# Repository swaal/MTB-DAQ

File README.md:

# MTB DAQ
A small and portable data acquisition system based on the PyBoard V1.1 designed to collect acceleration data while riding a mountain bike.

## About
The Mountain Bike Data Acquisition System (MTB DAQ) is a system designed to collect acceleration data while riding a mountain bike.
The system was designed as part of a Cal Poly Masters Thesis in Mechanical Engineering focused on a quantitative method for tuning mountain bike suspension. The MTB DAQ
was designed after the PyBoard V1.1 and is utilizes the same firmware. The acceleration data is stored in binary format on a Micro SD card. 

## Contents
The files included in this project provide almost everything needed to build a MTB DAQ. The folders are arranged as follows:
### BoardFiles
This folder contains all of the Autodesk Eagle schematic and board files. There are three types of boards: the Main Board, the UI Board, and the ADXL375 Board. 
The Main Board and UI Board work together to define the heart of the system, providing the computing power and user interface. The ADXL375 Board provides the necessary power filtering and connections for the ADXL375 accelerometer. The accelerometers are connected to the main board via two ethernet cables, chosen for their wide availability, low cost, and locking connection.
### MATLAB_Code
This folder contains two MATLAB files that can be used to interpret and plot the acceleration data from the binary files that are saved from the MTB DAQ.
### MicropythonCode
This folder contains the micropython files that run the MTB DAQ. Note that some of the files have been saved as *.mpy* files. This is a bytecote version of the original file. This was done in order to make the files small enough to fit in the flash memory of the microcontroller. The original files are contained within the sub folder "files_converted_to_mpy". Any modifications made to the original *.py* files can be converted into *.mpy* files using the python cross compiler *mpy-cross*. To get the system running, simply load on all the files in the MicropythonCode folder (excluding the contents in the files_converted_to_mpy subfolder) and reboot the board.
### PyBoardFirmware
A copy of the compatible PyBoard V1.1 firmware.

## Technical Specifications
- **Accelerometers:** Analog Devices ADXL375BCCZ Accelerometer
- **Number of Accelerometers Supported:** 2
- **Measurement Range:** +/- 200g
- **Output Data Rate:** 1600Hz (can be configured to go up to 3200Hz)
- **Battery Life:** > 8 hours

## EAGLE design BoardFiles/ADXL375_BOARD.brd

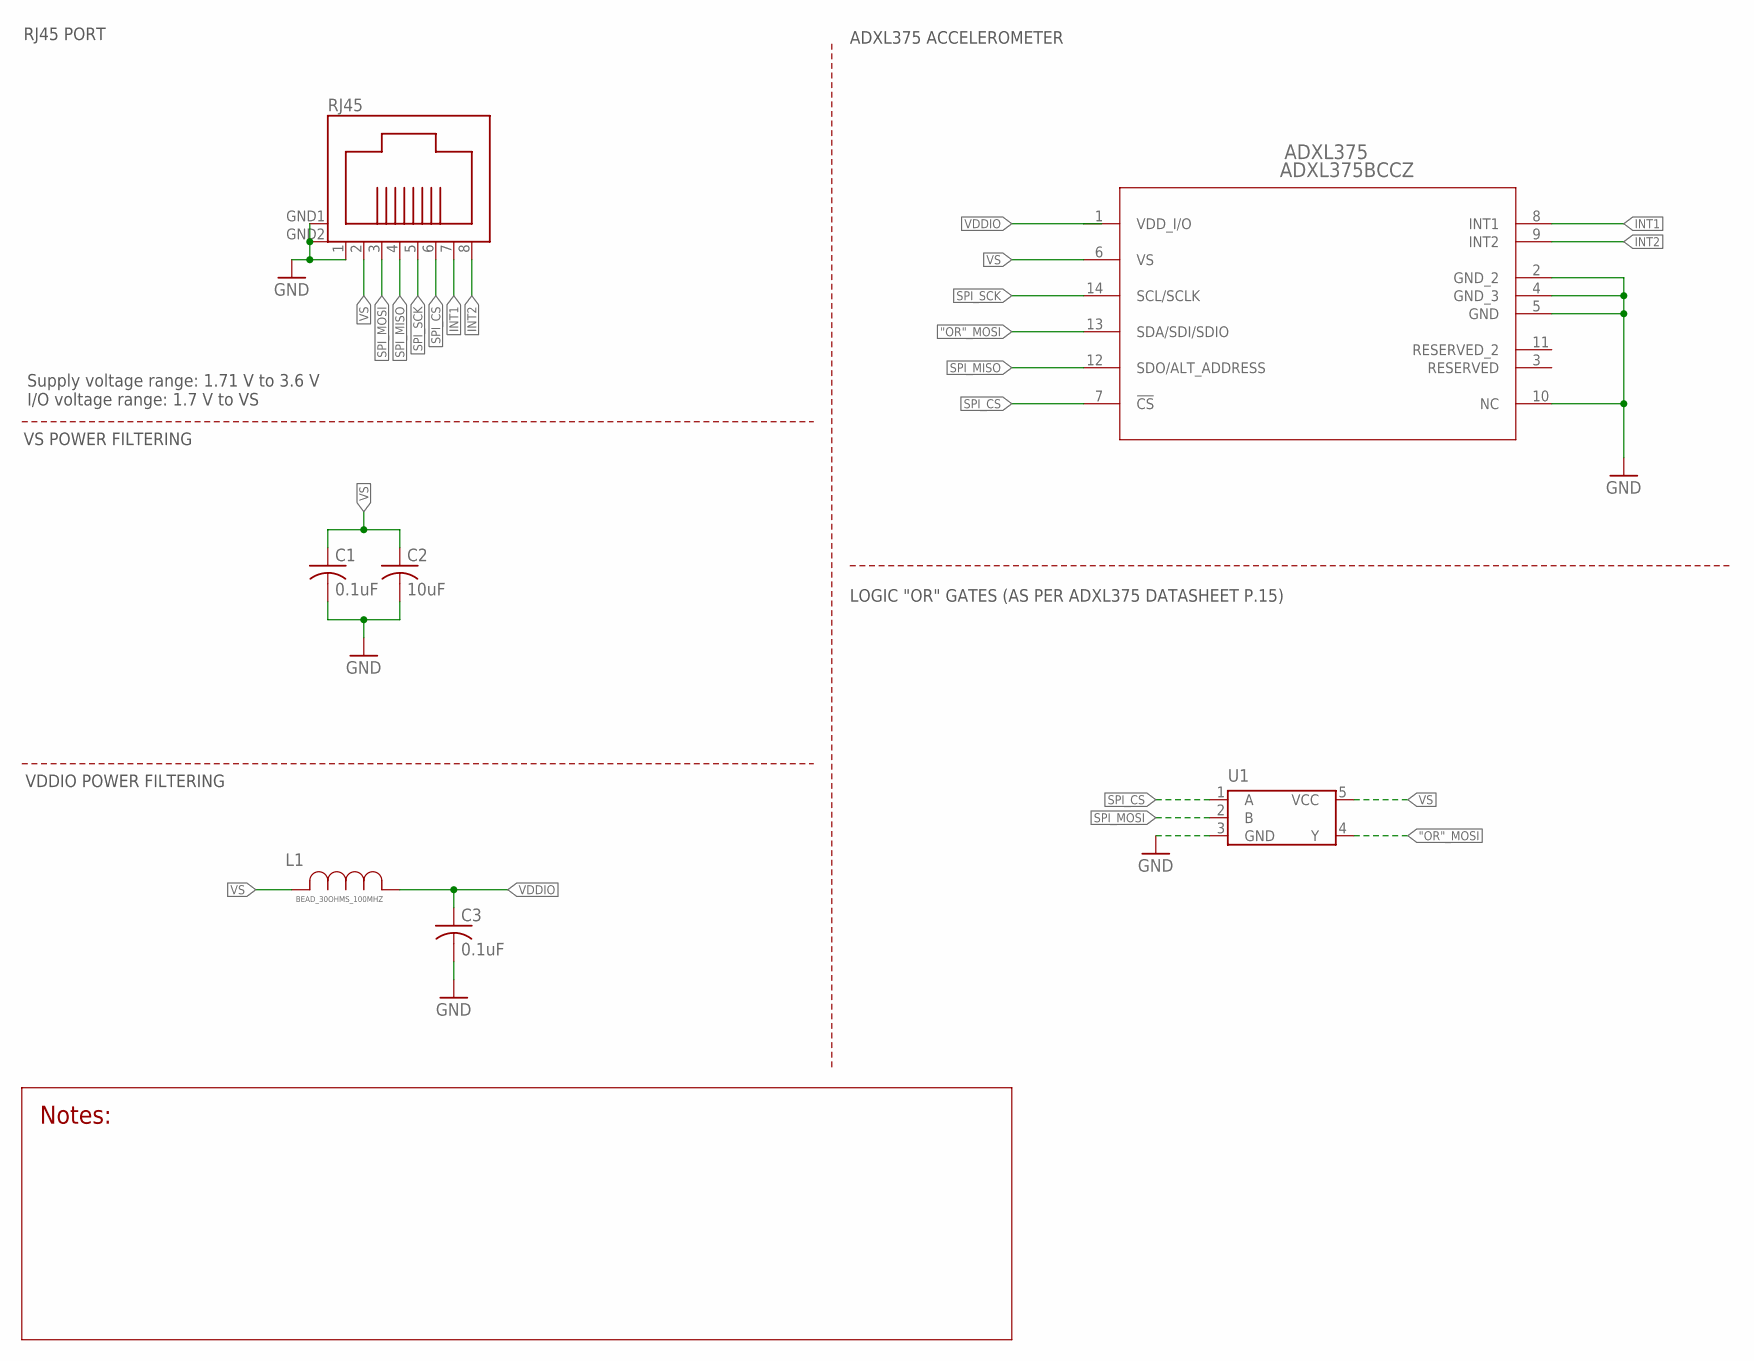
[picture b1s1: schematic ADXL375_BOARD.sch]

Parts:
ADXL375: ADXL375BCCZ; LGA_CC-14-1
C1, C3: 0.1uF; C0805
C2: 10uF; C0805
L1: BEAD_30OHMS_100MHZ; IND_BOURNS_MH2029
RJ45: RJ45_SURFACE_MOUNT
U1: SN74LVC1G32DCKR; DCK5

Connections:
"OR"_MOSI: ADXL375.13 (SDA/SDI/SDIO), U1.4 (Y)
GND: ADXL375.2 (GND_2), ADXL375.4 (GND_3), ADXL375.5 (GND), ADXL375.10 (NC), C1.2, C2.2, C3.2, RJ45.1, RJ45.GND1, RJ45.GND2, U1.3 (GND)
INT1: ADXL375.8 (INT1), RJ45.7
INT2: ADXL375.9 (INT2), RJ45.8
SPI_CS: ADXL375.7 (!CS), RJ45.6, U1.1 (A)
SPI_MISO: ADXL375.12 (SDO/ALT_ADDRESS), RJ45.4
SPI_MOSI: RJ45.3, U1.2 (B)
SPI_SCK: ADXL375.14 (SCL/SCLK), RJ45.5
VDDIO: ADXL375.1 (VDD_I/O), C3.1, L1.1
VS: ADXL375.6 (VS), C1.1, C2.1, L1.2, RJ45.2, U1.5 (VCC)

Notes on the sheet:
Supply voltage range: 1.71 V to 3.6 V I/O voltage range: 1.7 V to VS
RJ45 PORT
VS POWER FILTERING
VDDIO POWER FILTERING
LOGIC "OR" GATES (AS PER ADXL375 DATASHEET P.15)
ADXL375 ACCELEROMETER

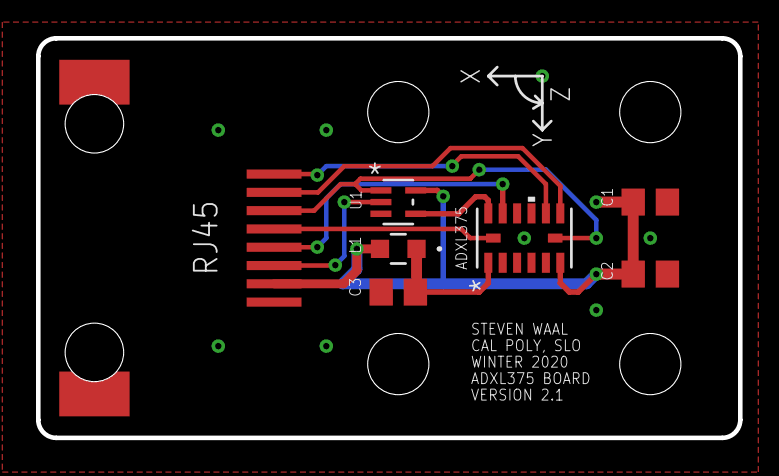
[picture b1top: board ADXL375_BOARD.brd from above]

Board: 2 copper layers, 39.0 x 22.2 mm, 7 parts (0 on the bottom side), 10 nets.

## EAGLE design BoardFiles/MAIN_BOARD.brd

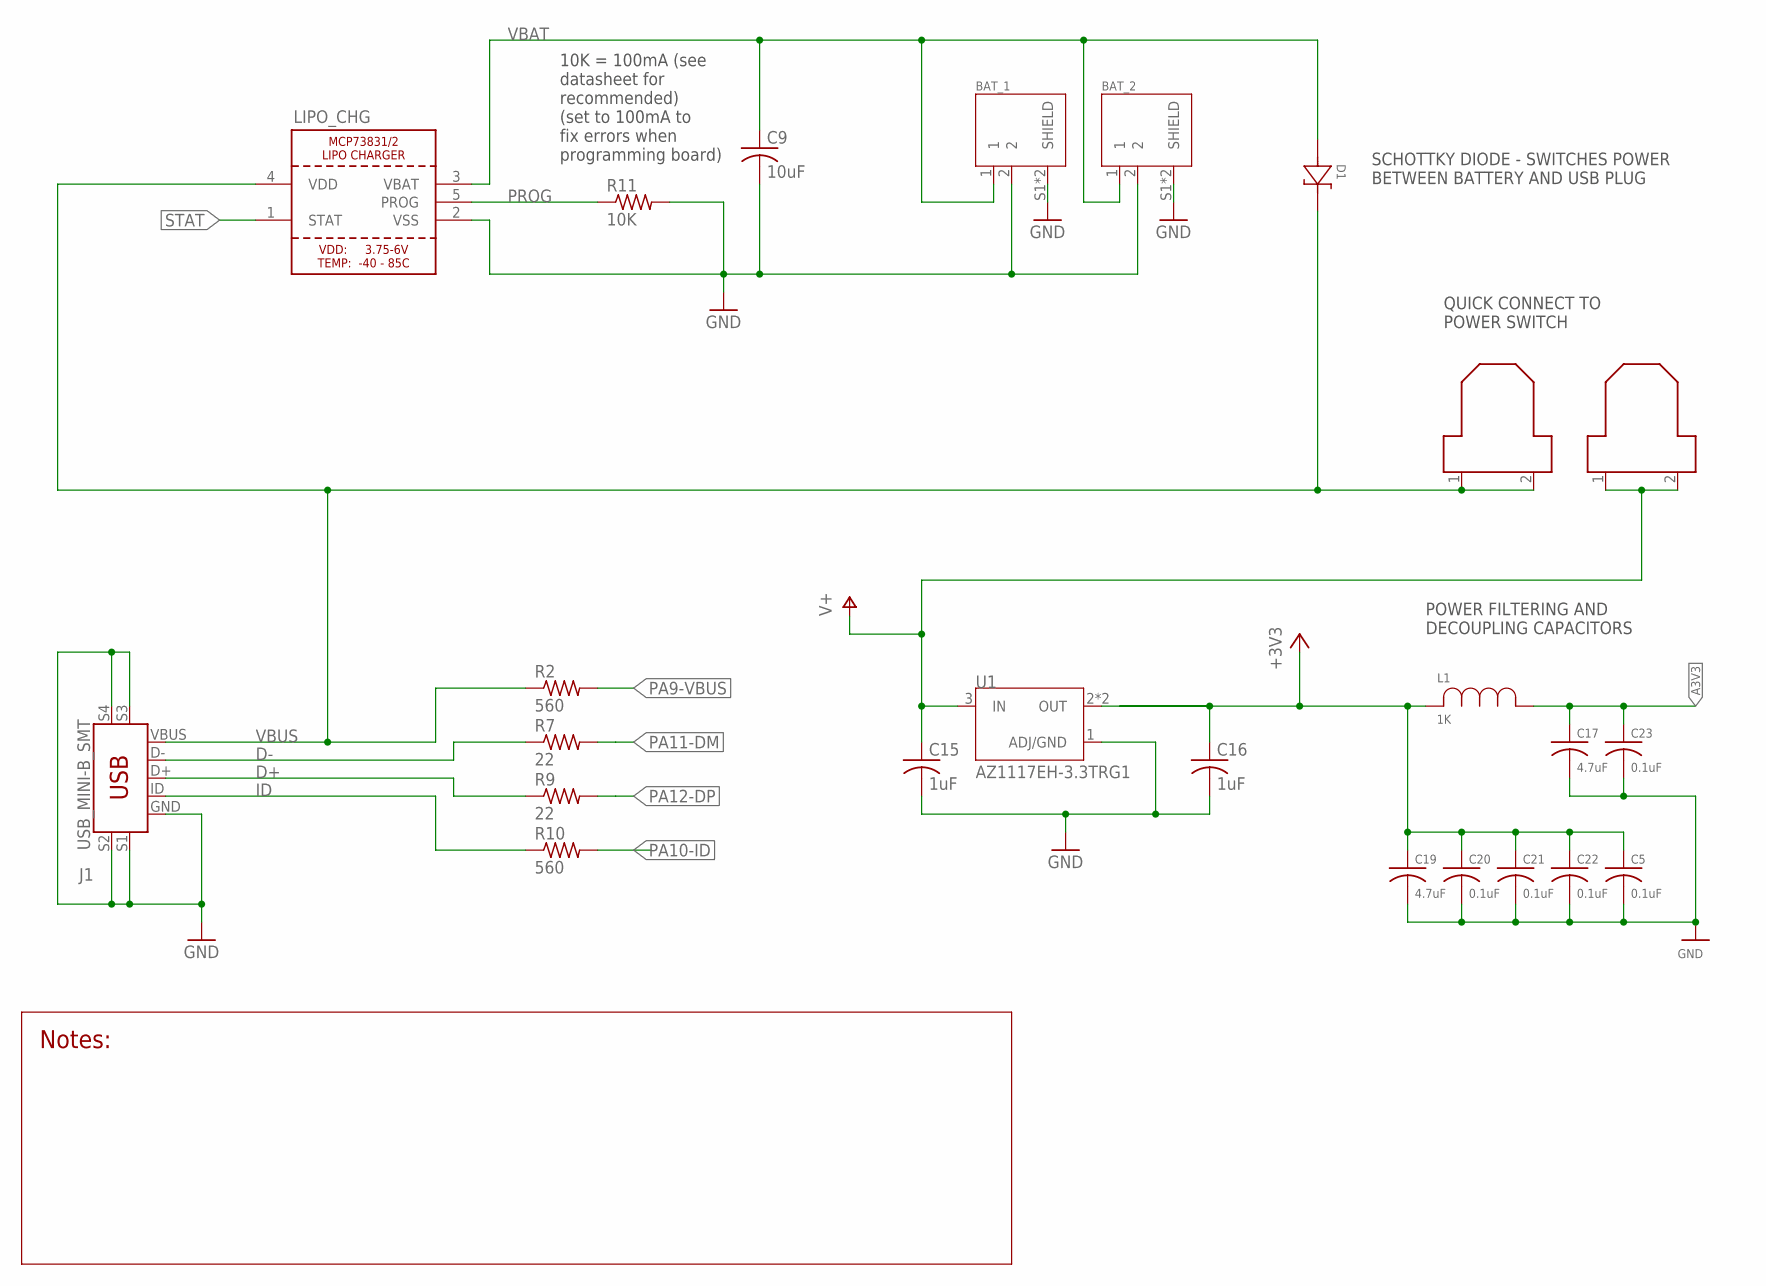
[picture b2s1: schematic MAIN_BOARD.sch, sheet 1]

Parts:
(+): QUICK_CONNECT_0.187"
(-): QUICK_CONNECT_0.187"
BAT_1, BAT_2: S2B-PH-SM4-TB(LF)(SN); JST_S2B-PH-SM4-TB(LF)(SN)
C5, C20, C21, C22, C23: 0.1uF; C0805
C9: 10uF; C0805
C15, C16: 1uF; C0805
C17, C19: 4.7uF; C0805
D1: DIODE_SCHOTTKY; DIODE_SOD123W_1P9X2P8
J1: USB_MINI-B_SMT; USB-MINIB
L1: 1K; IND_VISHAY_ILHB0805
LIPO_CHG: LIPO_CHARGER_MCP73831/2; SOT23-5
R2, R10: 560; R0805
R7, R9: 22; R0805
R11: 10K; R0805
U1: AZ1117EH-3.3TRG1; SOT230P700X180-4N

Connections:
+3V3: C5.1, C16.1, C19.1, C20.1, C21.1, C22.1, L1.2, U1.2 (OUT), U1.4 (OUT); also elsewhere on the board
A3V3: C17.1, C23.1, L1.1; also elsewhere on the board
D+: J1.D+, R9.1
D-: J1.D-, R7.1
GND: BAT_1.2, BAT_1.S1 (SHIELD), BAT_1.S2 (SHIELD), BAT_2.2, BAT_2.S1 (SHIELD), BAT_2.S2 (SHIELD), C5.2, C9.2, C15.2, C16.2, C17.2, C19.2, C20.2, C21.2, C22.2, C23.2, J1.GND, J1.S1 (SHIELD), J1.S2 (SHIELD1), J1.S3 (SHIELD2), J1.S4 (SHIELD3), LIPO_CHG.2 (VSS), R11.2, U1.1 (ADJ/GND); also elsewhere on the board
ID: J1.ID, R10.1
PA9-VBUS: R2.2; also elsewhere on the board
PA10-ID: R10.2; also elsewhere on the board
PA11-DM: R7.2; also elsewhere on the board
PA12-DP: R9.2; also elsewhere on the board
PROG: LIPO_CHG.5 (PROG), R11.1
STAT: LIPO_CHG.1 (STAT); also elsewhere on the board
V+: (-).1, (-).2, C15.1, U1.3 (IN)
VBAT: BAT_1.1, BAT_2.1, C9.1, D1.2, LIPO_CHG.3 (VBAT)
VBUS: (+).1, (+).2, D1.1, J1.VBUS, LIPO_CHG.4 (VDD), R2.1; also elsewhere on the board

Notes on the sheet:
10K = 100mA (see datasheet for recommended) (set to 100mA to fix errors when programming board)
SCHOTTKY DIODE - SWITCHES POWER BETWEEN BATTERY AND USB PLUG
POWER FILTERING AND DECOUPLING CAPACITORS
QUICK CONNECT TO POWER SWITCH

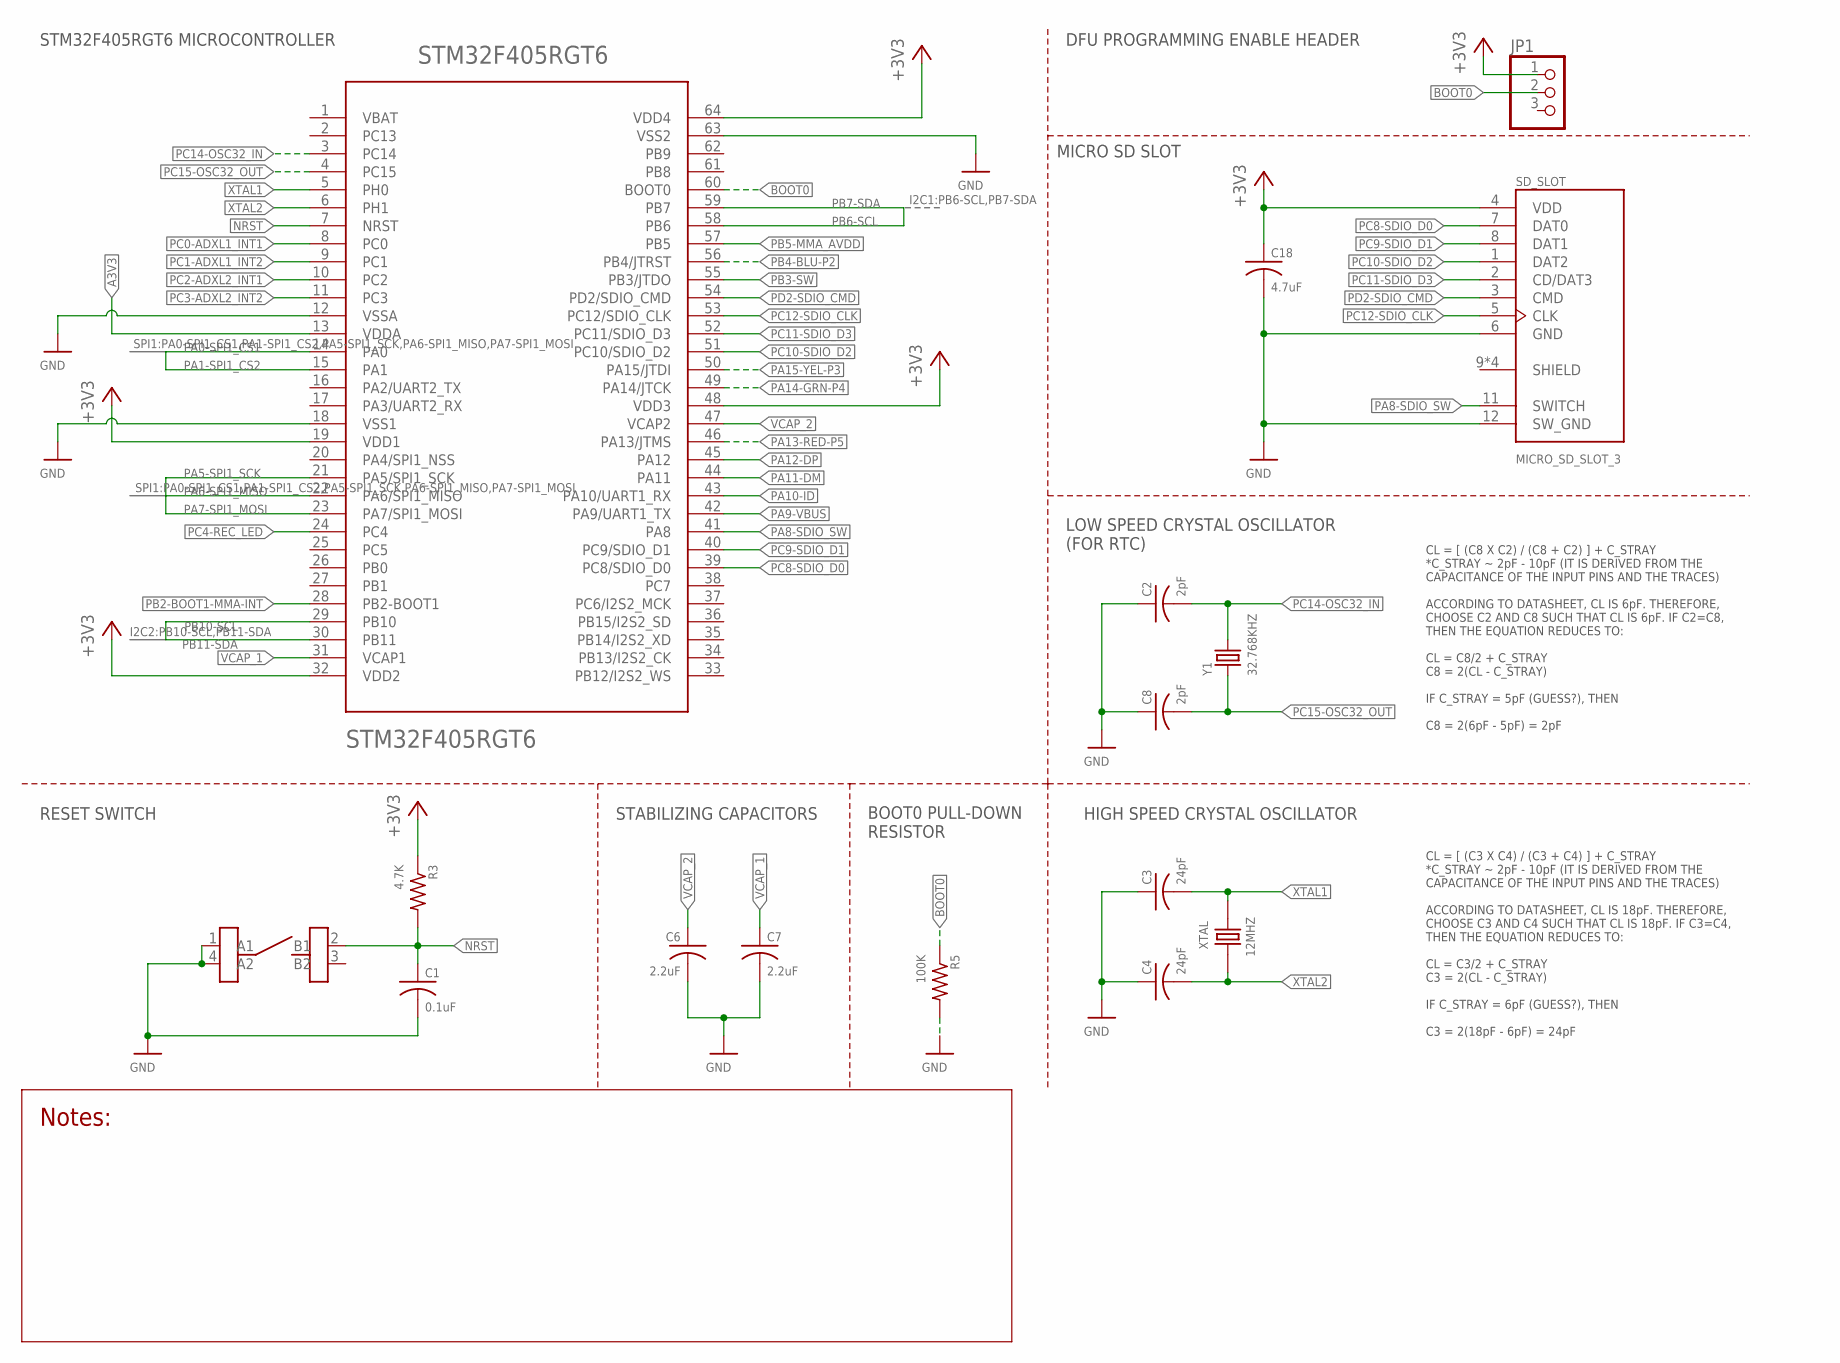
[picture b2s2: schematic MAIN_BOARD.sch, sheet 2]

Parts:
C1: 0.1uF; C0805
C2, C8: 2pF; C0805
C3, C4: 24pF; C0805
C6, C7: 2.2uF; C0805
C18: 4.7uF; C0805
JP1: PINHD-1X3; 1X03
R3: 4.7K; R0805
R5: 100K; R0805
RESET: SWITCH; SWITCH_FSM6JSMATR
SD_SLOT: MICRO_SD_SLOT_3; CON00218_8
STM32F405RGT6: STM32F405RGT6; TQFP64
XTAL: 12MHZ; XTAL_ECS-120-18-5PX-TR
Y1: 32.768KHZ; XTAL_ABS25-32.768KHZ-6-1-T

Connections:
+3V3: C18.1, JP1.1, R3.1, SD_SLOT.4 (VDD), STM32F405RGT6.19 (VDD1), STM32F405RGT6.32 (VDD2), STM32F405RGT6.48 (VDD3), STM32F405RGT6.64 (VDD4); also elsewhere on the board
A3V3: STM32F405RGT6.13 (VDDA); also elsewhere on the board
BOOT0: JP1.2, R5.1, STM32F405RGT6.60 (BOOT0)
GND: C1.2, C2.1, C3.1, C4.1, C6.2, C7.2, C8.1, C18.2, R5.2, RESET.1 (A1), RESET.4 (A2), SD_SLOT.6 (GND), SD_SLOT.12 (SW_GND), STM32F405RGT6.12 (VSSA), STM32F405RGT6.18 (VSS1), STM32F405RGT6.63 (VSS2); also elsewhere on the board
NRST: C1.1, R3.2, RESET.2 (B1), STM32F405RGT6.7 (NRST)
PA0-SPI1_CS1: STM32F405RGT6.14 (PA0); also elsewhere on the board
PA1-SPI1_CS2: STM32F405RGT6.15 (PA1); also elsewhere on the board
PA5-SPI1_SCK: STM32F405RGT6.21 (PA5/SPI1_SCK); also elsewhere on the board
PA6-SPI1_MISO: STM32F405RGT6.22 (PA6/SPI1_MISO); also elsewhere on the board
PA7-SPI1_MOSI: STM32F405RGT6.23 (PA7/SPI1_MOSI); also elsewhere on the board
PA8-SDIO_SW: SD_SLOT.11 (SWITCH), STM32F405RGT6.41 (PA8)
PA9-VBUS: STM32F405RGT6.42 (PA9/UART1_TX); also elsewhere on the board
PA10-ID: STM32F405RGT6.43 (PA10/UART1_RX); also elsewhere on the board
PA11-DM: STM32F405RGT6.44 (PA11); also elsewhere on the board
PA12-DP: STM32F405RGT6.45 (PA12); also elsewhere on the board
PA13-RED-P5: STM32F405RGT6.46 (PA13/JTMS); also elsewhere on the board
PA14-GRN-P4: STM32F405RGT6.49 (PA14/JTCK); also elsewhere on the board
PA15-YEL-P3: STM32F405RGT6.50 (PA15/JTDI); also elsewhere on the board
PB2-BOOT1-MMA-INT: STM32F405RGT6.28 (PB2-BOOT1); also elsewhere on the board
PB3-SW: STM32F405RGT6.55 (PB3/JTDO); also elsewhere on the board
PB4-BLU-P2: STM32F405RGT6.56 (PB4/JTRST); also elsewhere on the board
PB5-MMA_AVDD: STM32F405RGT6.57 (PB5); also elsewhere on the board
PB6-SCL: STM32F405RGT6.58 (PB6); also elsewhere on the board
PB7-SDA: STM32F405RGT6.59 (PB7); also elsewhere on the board
PB10-SCL: STM32F405RGT6.29 (PB10); also elsewhere on the board
PB11-SDA: STM32F405RGT6.30 (PB11); also elsewhere on the board
PC0-ADXL1_INT1: STM32F405RGT6.8 (PC0); also elsewhere on the board
PC1-ADXL1_INT2: STM32F405RGT6.9 (PC1); also elsewhere on the board
PC2-ADXL2_INT1: STM32F405RGT6.10 (PC2); also elsewhere on the board
PC3-ADXL2_INT2: STM32F405RGT6.11 (PC3); also elsewhere on the board
PC4-REC_LED: STM32F405RGT6.24 (PC4); also elsewhere on the board
PC8-SDIO_D0: SD_SLOT.7 (DAT0), STM32F405RGT6.39 (PC8/SDIO_D0)
PC9-SDIO_D1: SD_SLOT.8 (DAT1), STM32F405RGT6.40 (PC9/SDIO_D1)
PC10-SDIO_D2: SD_SLOT.1 (DAT2), STM32F405RGT6.51 (PC10/SDIO_D2)
PC11-SDIO_D3: SD_SLOT.2 (CD/DAT3), STM32F405RGT6.52 (PC11/SDIO_D3); also elsewhere on the board
PC12-SDIO_CLK: SD_SLOT.5 (CLK), STM32F405RGT6.53 (PC12/SDIO_CLK)
PC14-OSC32_IN: C2.2, STM32F405RGT6.3 (PC14), Y1.4 (2)
PC15-OSC32_OUT: C8.2, STM32F405RGT6.4 (PC15), Y1.1
PD2-SDIO_CMD: SD_SLOT.3 (CMD), STM32F405RGT6.54 (PD2/SDIO_CMD)
VCAP_1: C7.1, STM32F405RGT6.31 (VCAP1)
VCAP_2: C6.1, STM32F405RGT6.47 (VCAP2)
XTAL1: C3.2, STM32F405RGT6.5 (PH0), XTAL.2
XTAL2: C4.2, STM32F405RGT6.6 (PH1), XTAL.1

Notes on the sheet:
STM32F405RGT6 MICROCONTROLLER
RESET SWITCH
STABILIZING CAPACITORS
BOOT0 PULL-DOWN RESISTOR
HIGH SPEED CRYSTAL OSCILLATOR
CL = [ (C3 X C4) / (C3 + C4) ] + C_STRAY *C_STRAY ~ 2pF - 10pF (IT IS DERIVED FROM THE CAPACITANCE OF THE INPUT PINS AND THE TRACES) ACCORDING TO DATASHEET, CL IS 18pF. THEREFORE, CHOOSE C3 AND C4 SUCH THAT CL IS 18pF. IF C3=C4, THEN THE EQUATION REDUCES TO: CL = C3/2 + C_STRAY C3 = 2(CL - C_STRAY)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
CL = [ (C8 X C2) / (C8 + C2) ] + C_STRAY *C_STRAY ~ 2pF - 10pF (IT IS DERIVED FROM THE CAPACITANCE OF THE INPUT PINS AND THE TRACES) ACCORDING TO DATASHEET, CL IS 6pF. THEREFORE, CHOOSE C2 AND C8 SUCH THAT CL IS 6pF. IF C2=C8, THEN THE EQUATION REDUCES TO: CL = C8/2 + C_STRAY C8 = 2(CL - C_STRAY) I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
LOW SPEED CRYSTAL OSCILLATOR (FOR RTC)
MICRO SD SLOT
DFU PROGRAMMING ENABLE HEADER

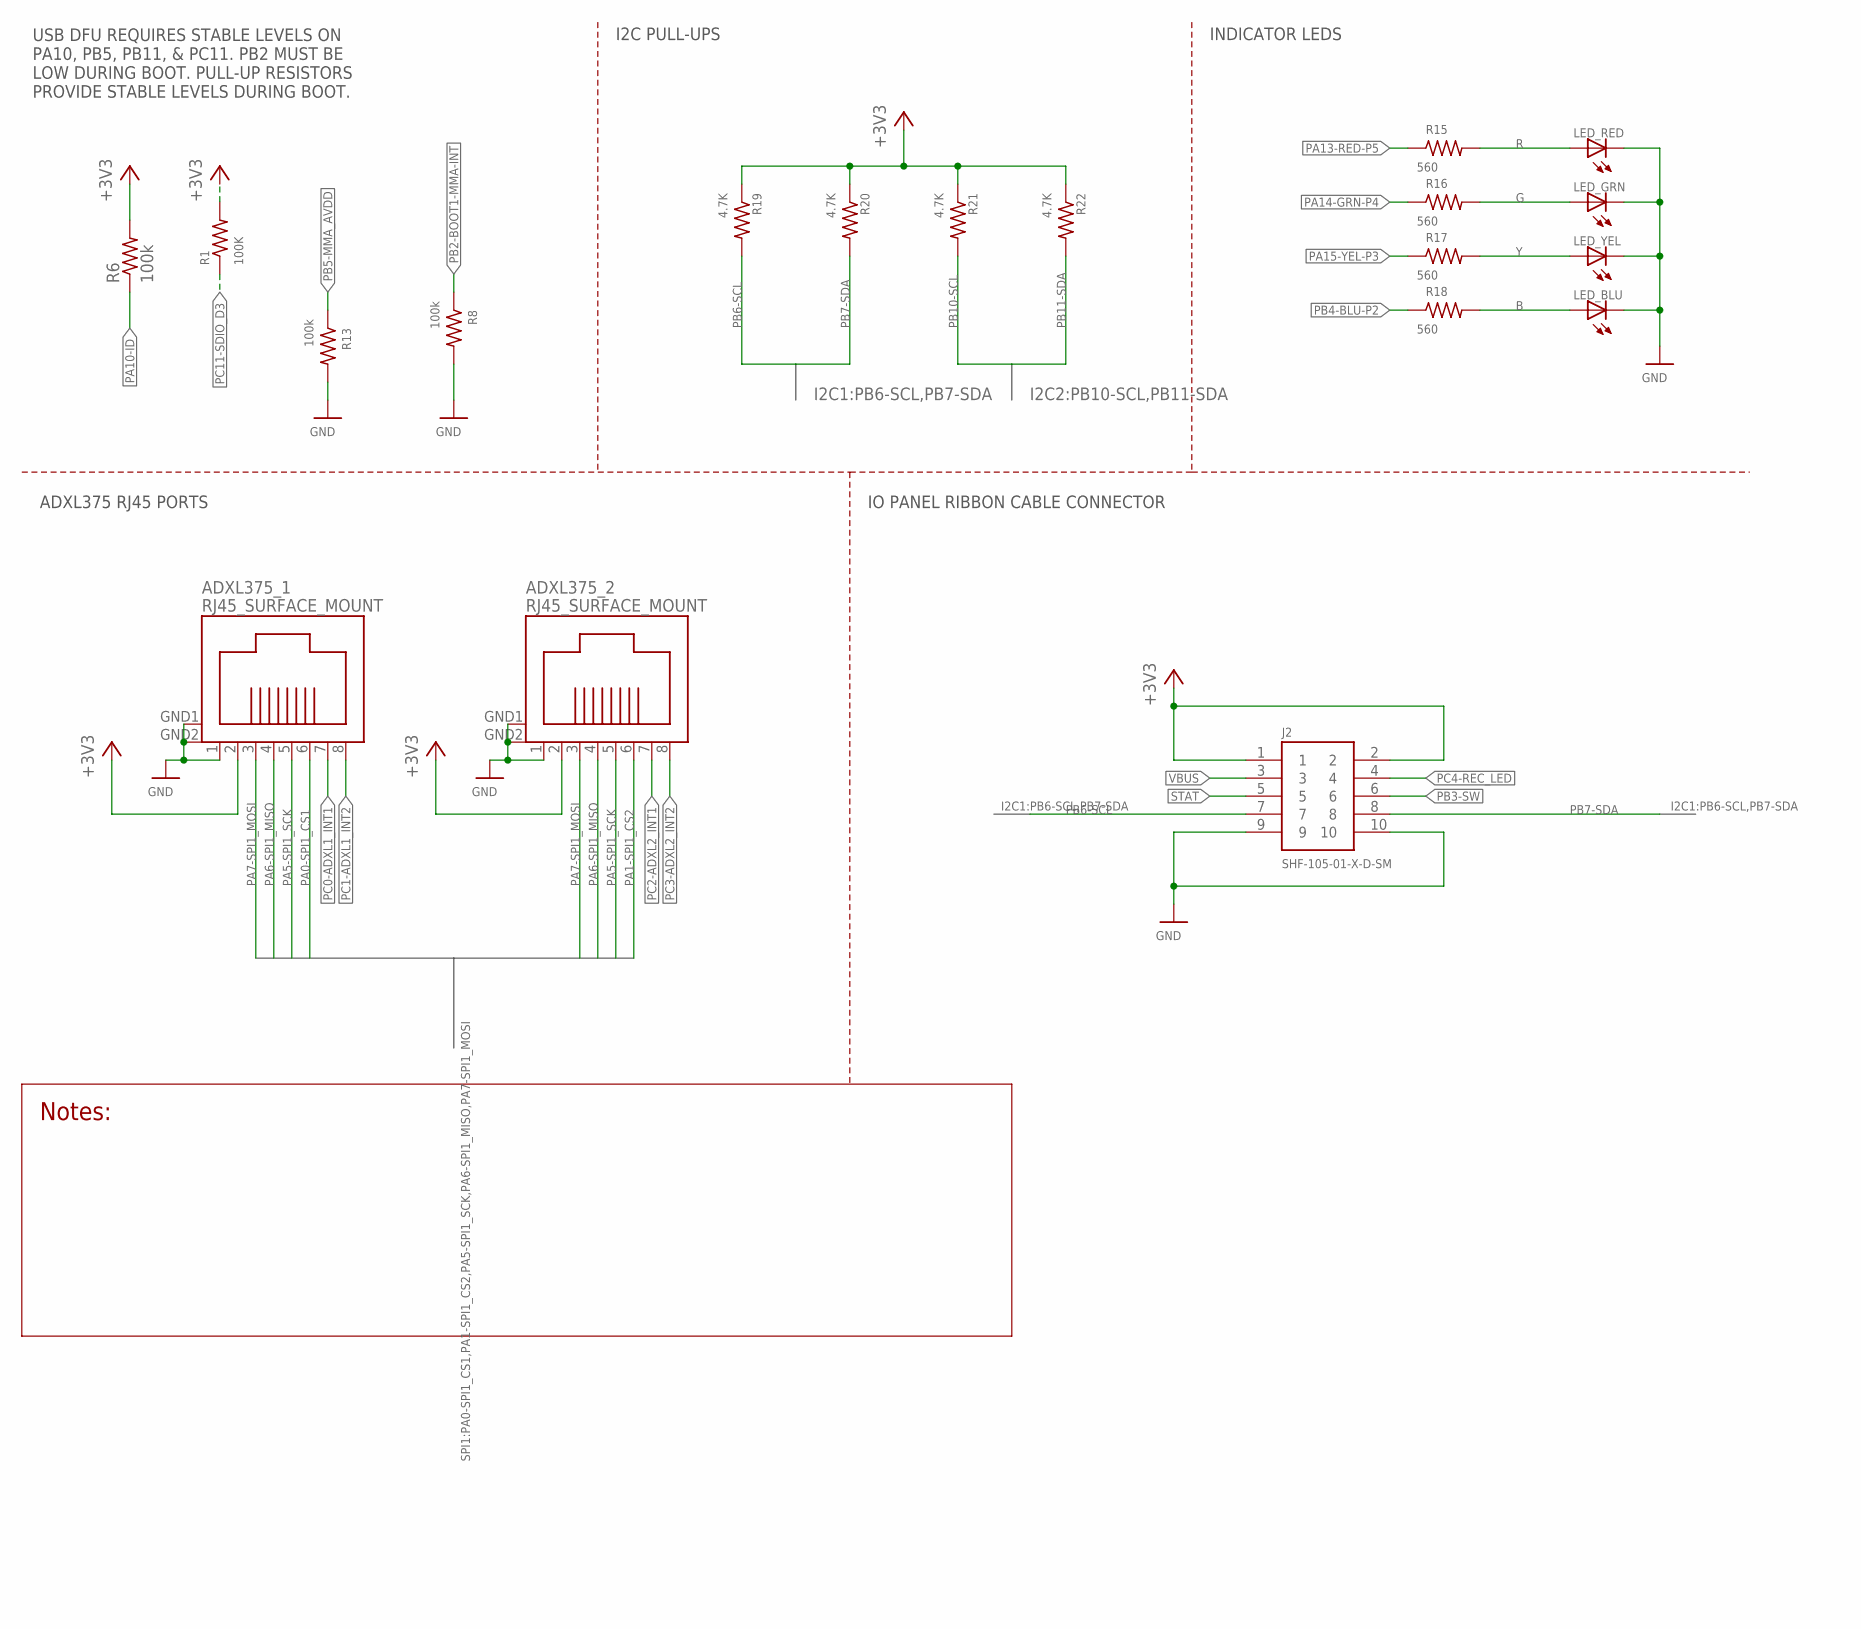
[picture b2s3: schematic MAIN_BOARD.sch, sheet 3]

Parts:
ADXL375_1, ADXL375_2: RJ45_SURFACE_MOUNT
J2: SHF-105-01-X-D-SM
LED_BLU: LED_0805LED_0805; 0805
LED_GRN: LED_0805LED_0805; 0805
LED_RED: LED_0805LED_0805; 0805
LED_YEL: LED_0805LED_0805; 0805
R1: 100K; R0805
R6, R8, R13: 100k; R0805
R15, R16, R17, R18: 560; R0805
R19, R20, R21, R22: 4.7K; R0805

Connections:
+3V3: ADXL375_1.2, ADXL375_2.2, J2.1, J2.2, R1.2, R6.2, R19.1, R20.1, R21.1, R22.1; also elsewhere on the board
B: LED_BLU.1, R18.2
G: LED_GRN.1, R16.2
GND: ADXL375_1.1, ADXL375_1.GND1, ADXL375_1.GND2, ADXL375_2.1, ADXL375_2.GND1, ADXL375_2.GND2, J2.9, J2.10, LED_BLU.2, LED_GRN.2, LED_RED.2, LED_YEL.2, R8.2, R13.2; also elsewhere on the board
PA0-SPI1_CS1: ADXL375_1.6; also elsewhere on the board
PA1-SPI1_CS2: ADXL375_2.6; also elsewhere on the board
PA5-SPI1_SCK: ADXL375_1.5, ADXL375_2.5; also elsewhere on the board
PA6-SPI1_MISO: ADXL375_1.4, ADXL375_2.4; also elsewhere on the board
PA7-SPI1_MOSI: ADXL375_1.3, ADXL375_2.3; also elsewhere on the board
PA10-ID: R6.1; also elsewhere on the board
PA13-RED-P5: R15.1; also elsewhere on the board
PA14-GRN-P4: R16.1; also elsewhere on the board
PA15-YEL-P3: R17.1; also elsewhere on the board
PB2-BOOT1-MMA-INT: R8.1; also elsewhere on the board
PB3-SW: J2.6; also elsewhere on the board
PB4-BLU-P2: R18.1; also elsewhere on the board
PB5-MMA_AVDD: R13.1; also elsewhere on the board
PB6-SCL: J2.7, R19.2; also elsewhere on the board
PB7-SDA: J2.8, R20.2; also elsewhere on the board
PB10-SCL: R21.2; also elsewhere on the board
PB11-SDA: R22.2; also elsewhere on the board
PC0-ADXL1_INT1: ADXL375_1.7; also elsewhere on the board
PC1-ADXL1_INT2: ADXL375_1.8; also elsewhere on the board
PC2-ADXL2_INT1: ADXL375_2.7; also elsewhere on the board
PC3-ADXL2_INT2: ADXL375_2.8; also elsewhere on the board
PC4-REC_LED: J2.4; also elsewhere on the board
PC11-SDIO_D3: R1.1; also elsewhere on the board
R: LED_RED.1, R15.2
STAT: J2.5; also elsewhere on the board
VBUS: J2.3; also elsewhere on the board
Y: LED_YEL.1, R17.2

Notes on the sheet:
INDICATOR LEDS
I2C PULL-UPS
USB DFU REQUIRES STABLE LEVELS ON PA10, PB5, PB11, & PC11. PB2 MUST BE LOW DURING BOOT. PULL-UP RESISTORS PROVIDE STABLE LEVELS DURING BOOT.
ADXL375 RJ45 PORTS
IO PANEL RIBBON CABLE CONNECTOR

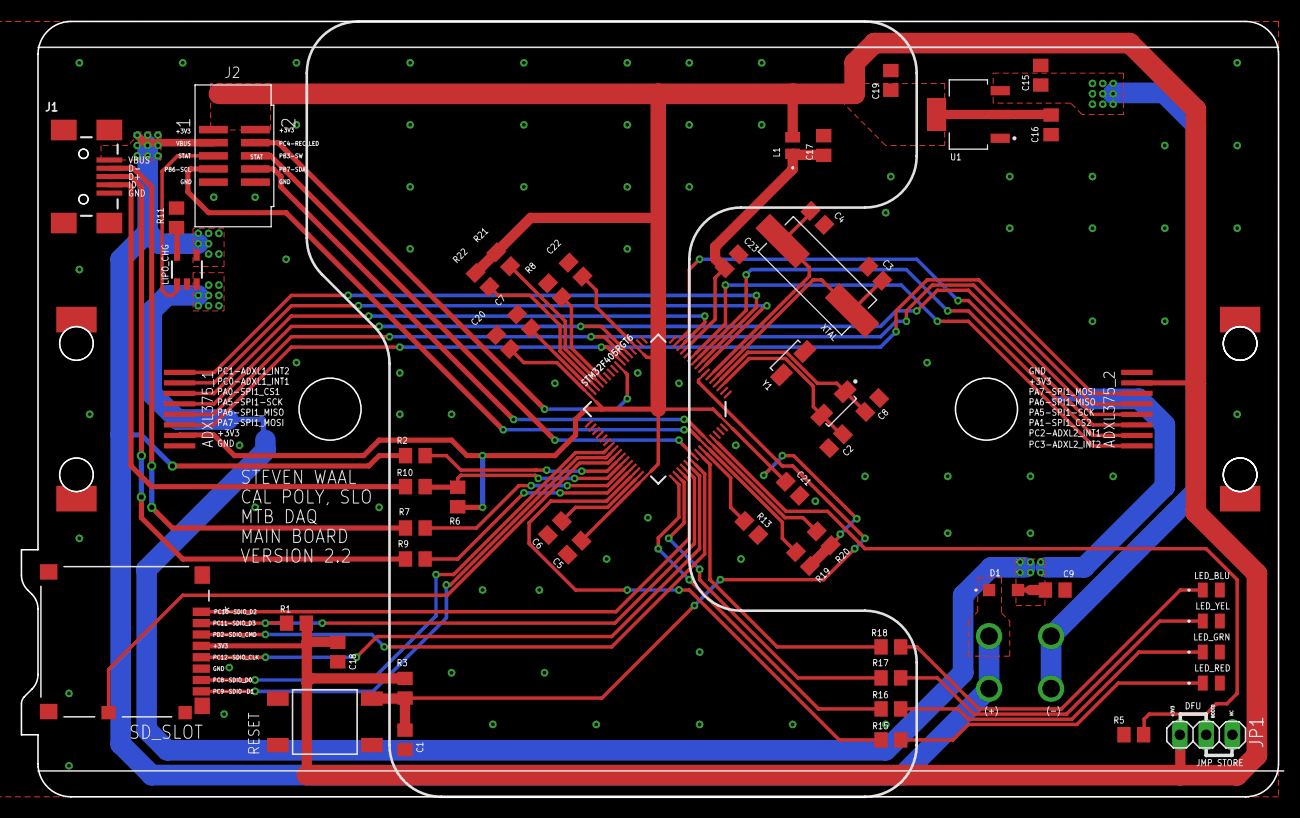
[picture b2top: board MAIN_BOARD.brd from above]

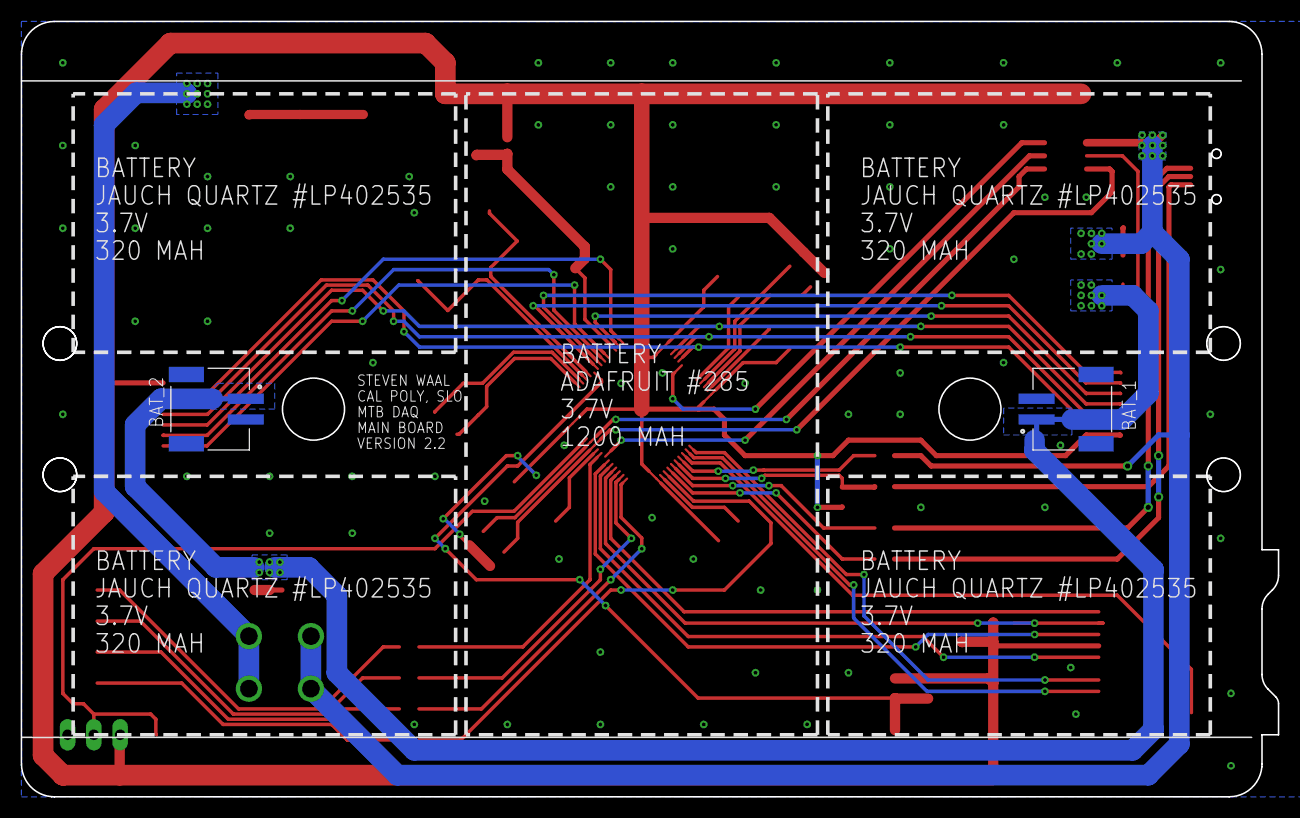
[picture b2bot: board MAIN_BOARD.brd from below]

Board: 2 copper layers, 121.6 x 75.0 mm, 59 parts (2 on the bottom side), 55 nets.

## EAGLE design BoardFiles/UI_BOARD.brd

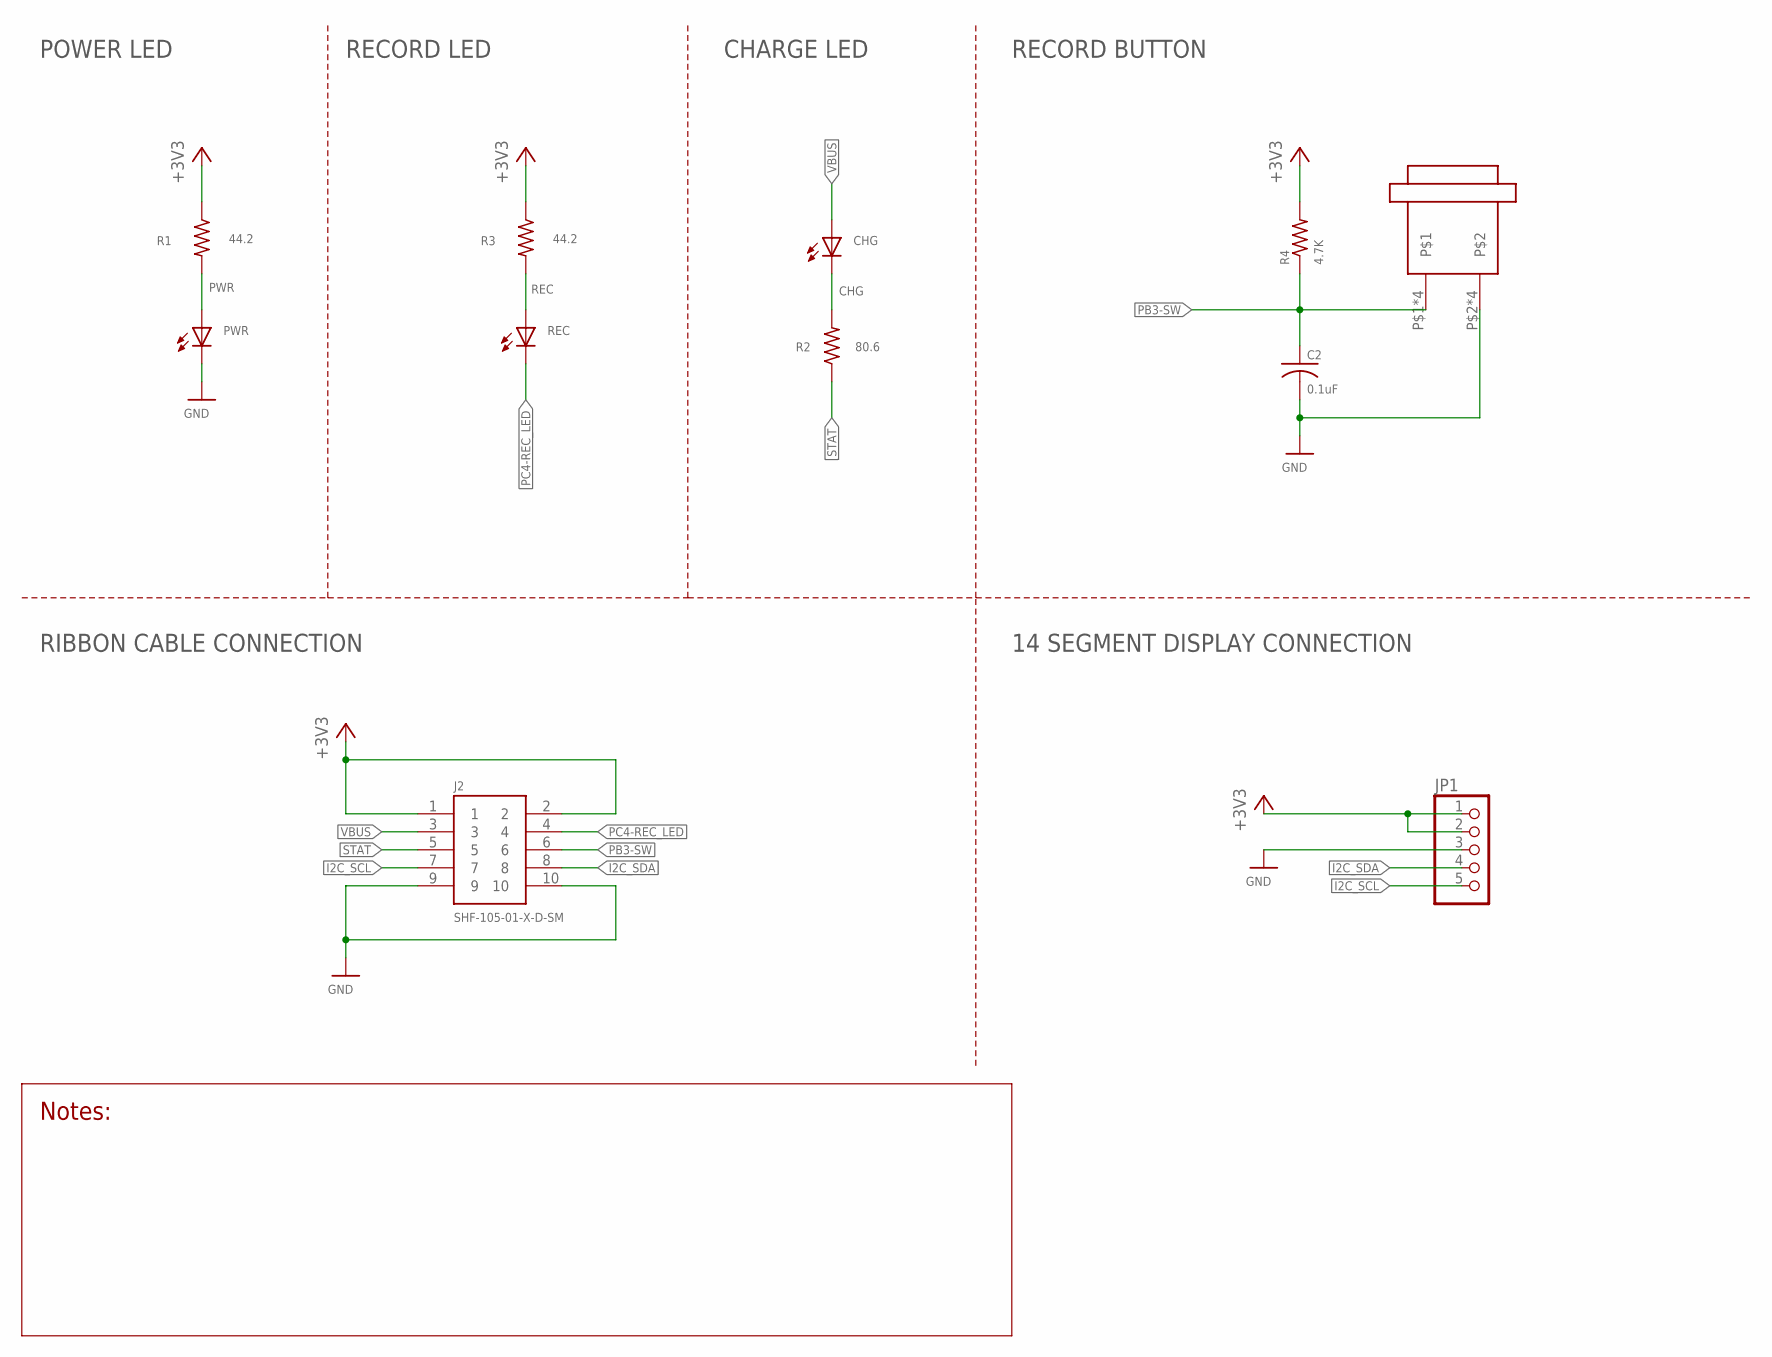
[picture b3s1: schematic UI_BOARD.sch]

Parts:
C2: 0.1uF; C0805
CHG: PANEL_MOUNT_LED
J2: SHF-105-01-X-D-SM
JP1: PINHD-1X5; 1X05
PWR: PANEL_MOUNT_LED
R1, R3: 44.2; R0805
R2: 80.6; R0805
R4: 4.7K; R0805
REC: PANEL_MOUNT_LED
U$4: PANEL_MOUNT_PUSH_BUTTON

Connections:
+3V3: J2.1, J2.2, JP1.1, JP1.2, R1.1, R3.1, R4.2
CHG: CHG.P$2 (2), R2.2
GND: C2.2, J2.9, J2.10, JP1.3, PWR.P$2 (2), U$4.P$2, U$4.P$4, U$4.P$6, U$4.P$8
I2C_SCL: J2.7, JP1.5
I2C_SDA: J2.8, JP1.4
PB3-SW: C2.1, J2.6, R4.1, U$4.P$1, U$4.P$3, U$4.P$5, U$4.P$7
PC4-REC_LED: J2.4, REC.P$2 (2)
PWR: PWR.P$1 (1), R1.2
REC: R3.2, REC.P$1 (1)
STAT: J2.5, R2.1
VBUS: CHG.P$1 (1), J2.3

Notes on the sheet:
POWER LED
RECORD LED
CHARGE LED
RECORD BUTTON
14 SEGMENT DISPLAY CONNECTION
RIBBON CABLE CONNECTION

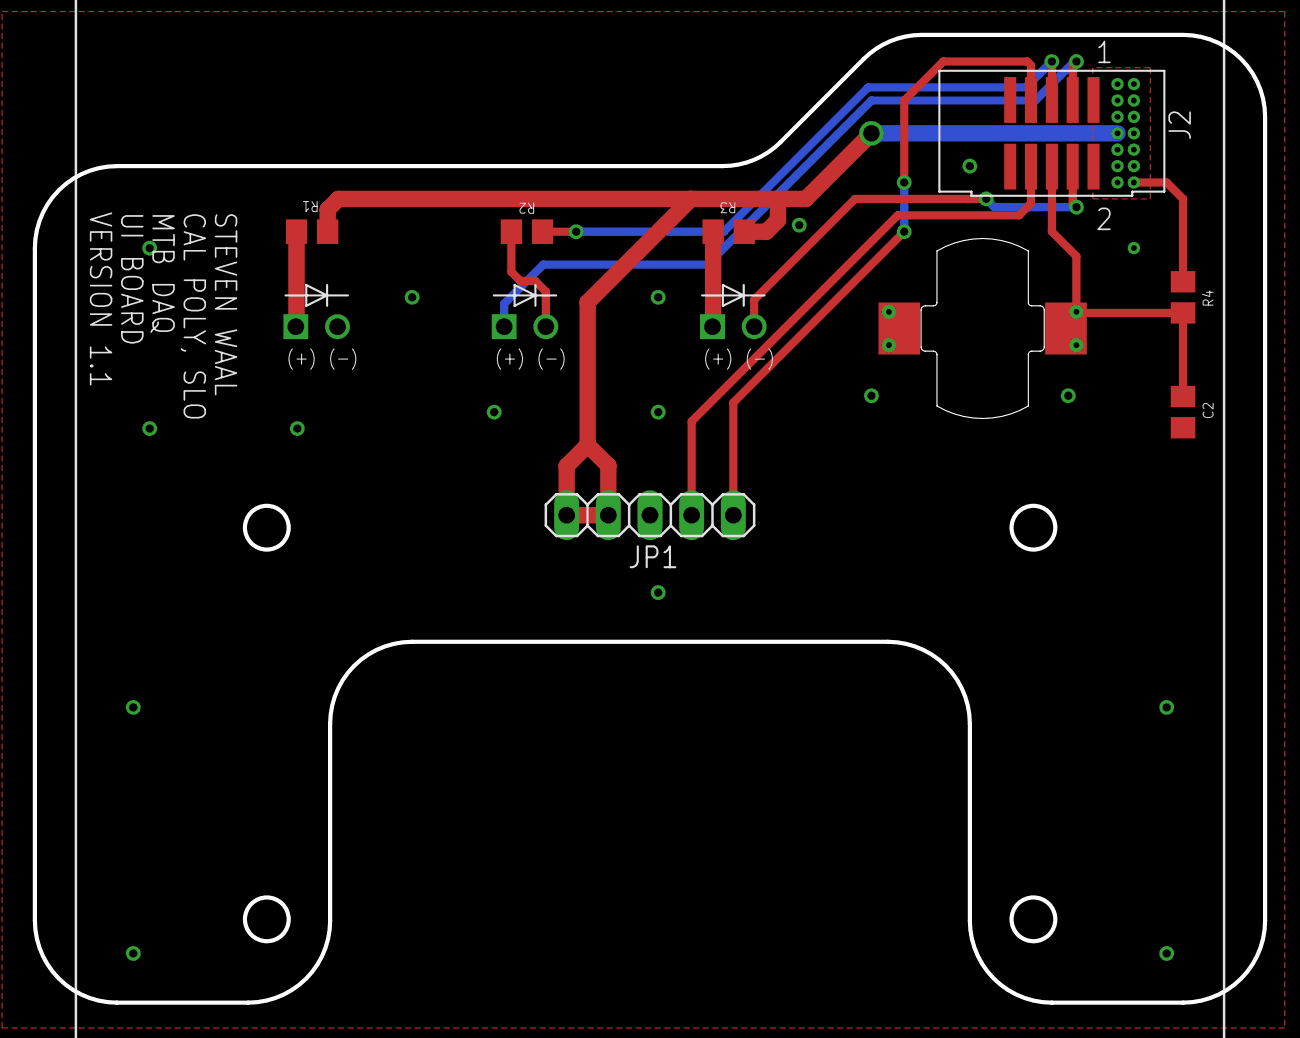
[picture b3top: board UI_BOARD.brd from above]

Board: 2 copper layers, 75.0 x 59.0 mm, 11 parts (0 on the bottom side), 11 nets.

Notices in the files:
parts and their libraries:
COPYRIGHT: Copyright (C) 2016 Accelerated Designs. All rights reserved
